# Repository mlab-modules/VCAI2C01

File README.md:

<!--- PrjInfo ---> <!--- Please remove this line after manually editing --->
<!--- 00a56be08b96043df9e37d6aff7b6990 --->
<!--- Created:2019-02-18 14:36:04.428293: ---> 
<!--- Author:: ---> 
<!--- AuthorEmail:: ---> 
<!--- Tags:: ---> 
<!--- Ust:: ---> 
<!--- Label --->
<!--- ELabel ---> 
<!--- Name:VCAI2C01A: --->
# VCAI2C01A
<!--- LongName --->
## AD converter voltage and current with I2C
<!--- ELongName ---> 

<!--- Lead --->
4-channel 18-bit AD converter voltage and current for industrial sensors. Ranges: 0-5V, 0-10V, 0-20mA, 4-20mA, 0-40 mA.
<!--- ELead ---> 

<!--- Description --->
<!--- EDescription --->
<!--- Content --->
<!--- EContent --->
<sub><sup> Generated with [MLABweb](https://github.com/MLAB-project/MLABweb). (2019-02-18)</sup></sub>

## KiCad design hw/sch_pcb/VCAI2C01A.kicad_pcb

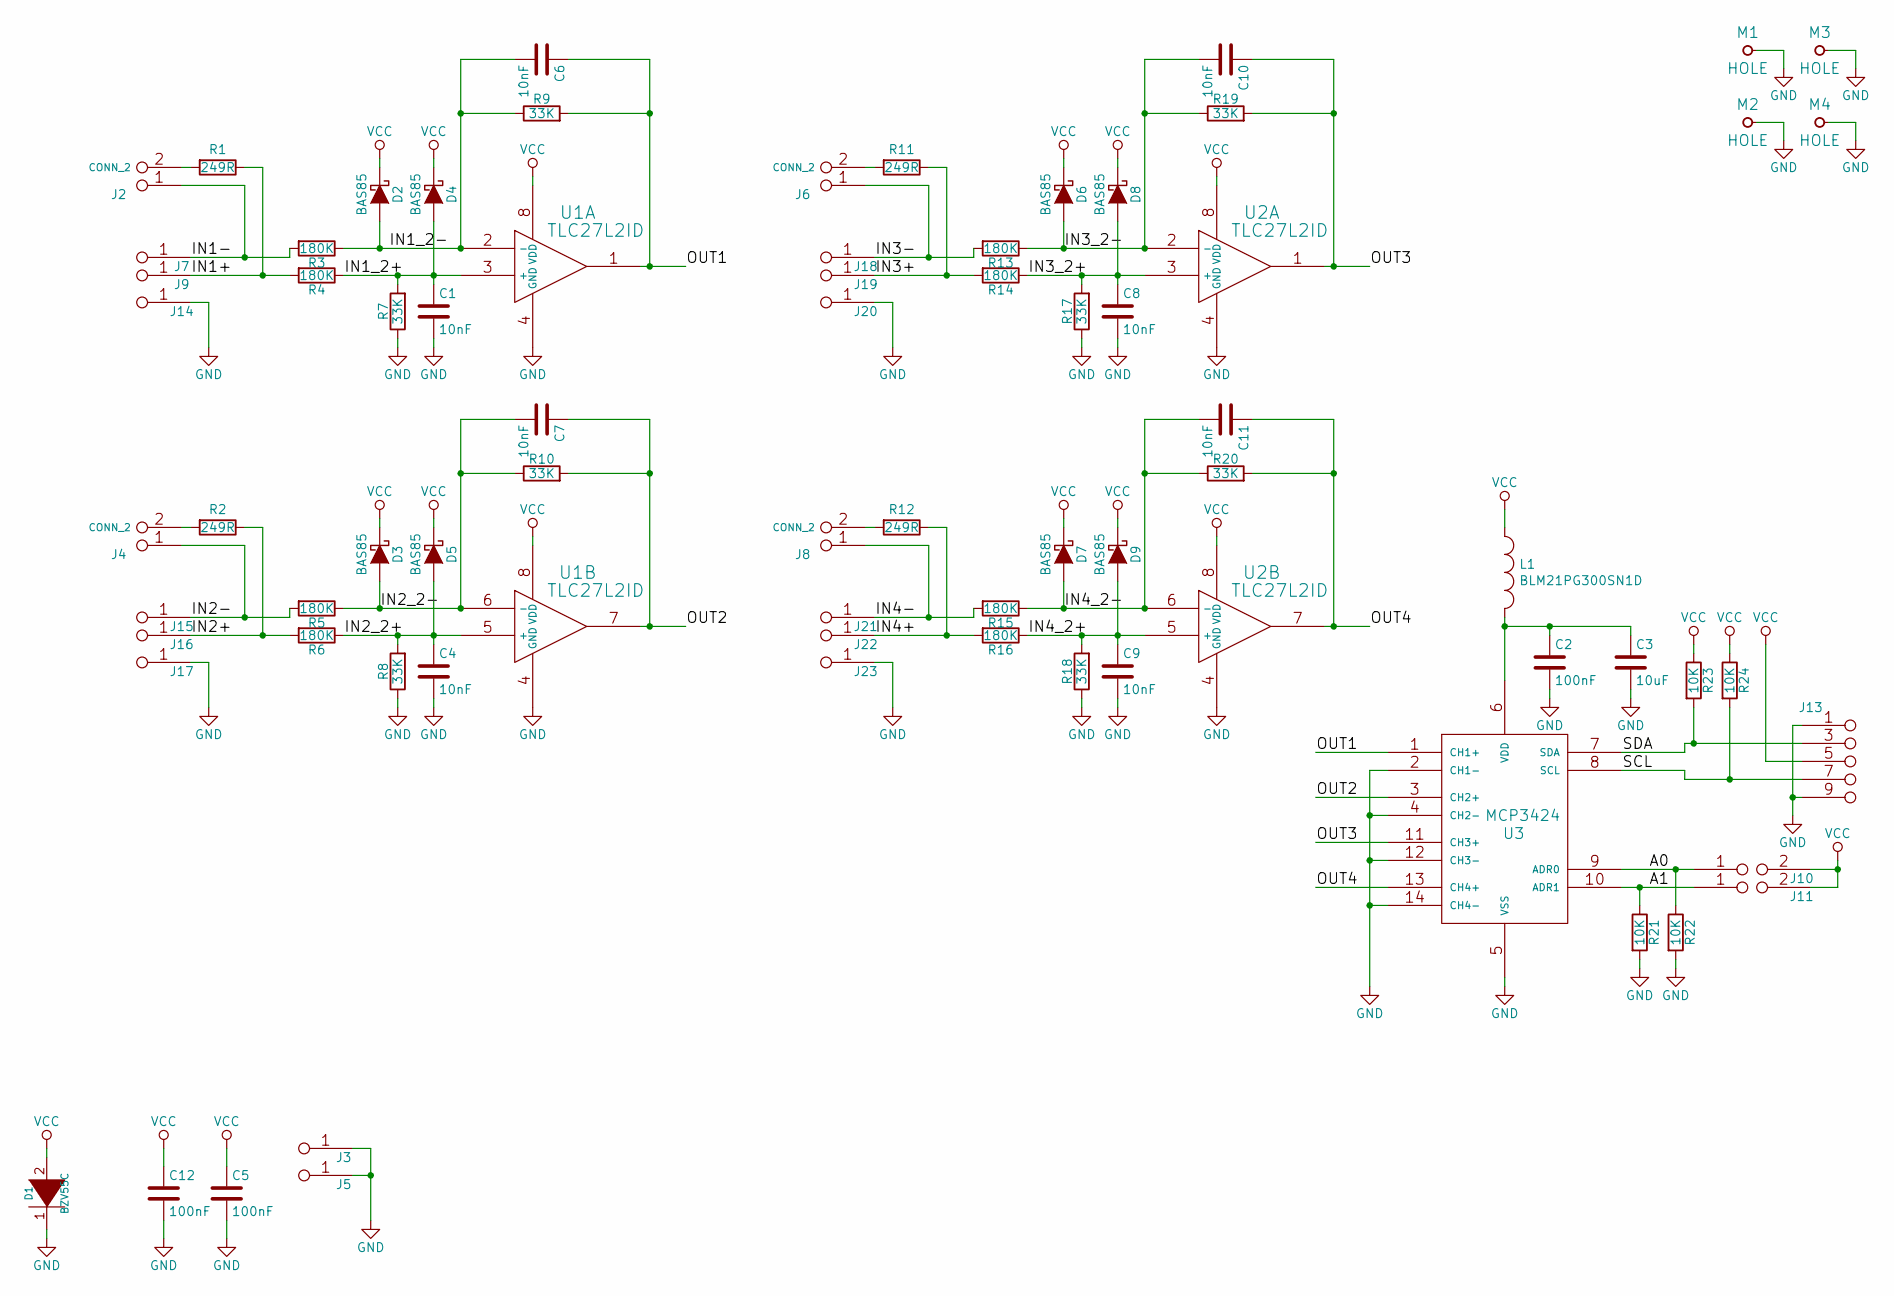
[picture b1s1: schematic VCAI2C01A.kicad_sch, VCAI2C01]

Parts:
C1, C4, C6, C7, C8, C9, C10, C11: 10nF; SMD-0805
C2, C5, C12: 100nF; SMD-0805
C3: 10uF; SMD-0805
D1: BZV55C; Diode-MiniMELF_Standard
D2, D3, D4, D5, D6, D7, D8, D9: BAS85; MiniMELF_Standard
J2, J4, J6, J8: CONN_2; Straight_1x02
J3: JUMP_2x1; Straight_2x01
J5, J7, J9, J14, J15, J16, J17, J18, J19, J20, J21, J22, J23: JUMP_2x1; Straight_1x02
J10, J11: JUMP2_2x1; Straight_2x01
J13: JUMP_5X2; Straight_2x05
L1: BLM21PG300SN1D; SMD-0805
M1, M2, M3, M4: HOLE; MountingHole_3mm
R1, R2, R11, R12: 249R; SMD-1206
R3, R4, R5, R6, R13, R14, R15, R16: 180K; SMD-0805
R7, R8, R9, R10, R17, R18, R19, R20: 33K; SMD-0805
R21, R22, R23, R24: 10K; SMD-0805
U1, U2: TLC27L2ID; SOIC-8_3.9x4.9mm_Pitch1.27mm
U3: MCP3424; SOIC-14

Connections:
/A0: J10.1, R22.1, U3.9 (ADR0)
/A1: J11.1, R21.1, U3.10 (ADR1)
/IN1+: J9.1, J9.2, R1.1, R4.2
/IN1-: J2.1, J7.1, J7.2, R3.2
/IN1_2+: C1.1, D4.2 (A), R4.1, R7.2, U1.3 (+)
/IN1_2-: C6.2, D2.2 (A), R3.1, R9.1, U1.2 (-)
/IN2+: J16.1, J16.2, R2.1, R6.2
/IN2-: J4.1, J15.1, J15.2, R5.2
/IN2_2+: C4.1, D5.2 (A), R6.1, R8.2, U1.5 (+)
/IN2_2-: C7.2, D3.2 (A), R5.1, R10.1, U1.6 (-)
/IN3+: J19.1, J19.2, R11.1, R14.2
/IN3-: J6.1, J18.1, J18.2, R13.2
/IN3_2+: C8.1, D8.2 (A), R14.1, R17.2, U2.3 (+)
/IN3_2-: C10.2, D6.2 (A), R13.1, R19.1, U2.2 (-)
/IN4+: J22.1, J22.2, R12.1, R16.2
/IN4-: J8.1, J21.1, J21.2, R15.2
/IN4_2+: C9.1, D9.2 (A), R16.1, R18.2, U2.5 (+)
/IN4_2-: C11.2, D7.2 (A), R15.1, R20.1, U2.6 (-)
/OUT1: C6.1, R9.2, U1.1, U3.1 (CH1+)
/OUT2: C7.1, R10.2, U1.7, U3.3 (CH2+)
/OUT3: C10.1, R19.2, U2.1, U3.11 (CH3+)
/OUT4: C11.1, R20.2, U2.7, U3.13 (CH4+)
/SCL: J13.7, J13.8 (7), R24.2, U3.8 (SCL)
/SDA: J13.3 (4), J13.4, R23.2, U3.7 (SDA)
GND: C1.2, C2.2, C3.2, C4.2, C5.2, C8.2, C9.2, C12.2, D1.1 (K), J3.1, J3.2, J5.1, J5.2, J13.1 (2), J13.2, J13.9 (10), J13.10, J14.1, J14.2, J17.1, J17.2, J20.1, J20.2, J23.1, J23.2, M1.1, M2.1, M3.1, M4.1, R7.1, R8.1, R17.1, R18.1, R21.2, R22.2, U1.4 (GND), U2.4 (GND), U3.2 (CH1-), U3.4 (CH2-), U3.5 (VSS), U3.12 (CH3-), U3.14 (CH4-)
unnamed: C2.1, C3.1, L1.2, U3.6 (VDD)
unnamed: J2.2 (PM), R1.2
unnamed: J4.2 (PM), R2.2
unnamed: J6.2 (PM), R11.2
unnamed: J8.2 (PM), R12.2
VCC: C5.1, C12.1, D1.2 (A), D2.1 (K), D3.1 (K), D4.1 (K), D5.1 (K), D6.1 (K), D7.1 (K), D8.1 (K), D9.1 (K), J10.2, J11.2, J13.5 (6), J13.6, L1.1, R23.1, R24.1, U1.8 (VDD), U2.8 (VDD)

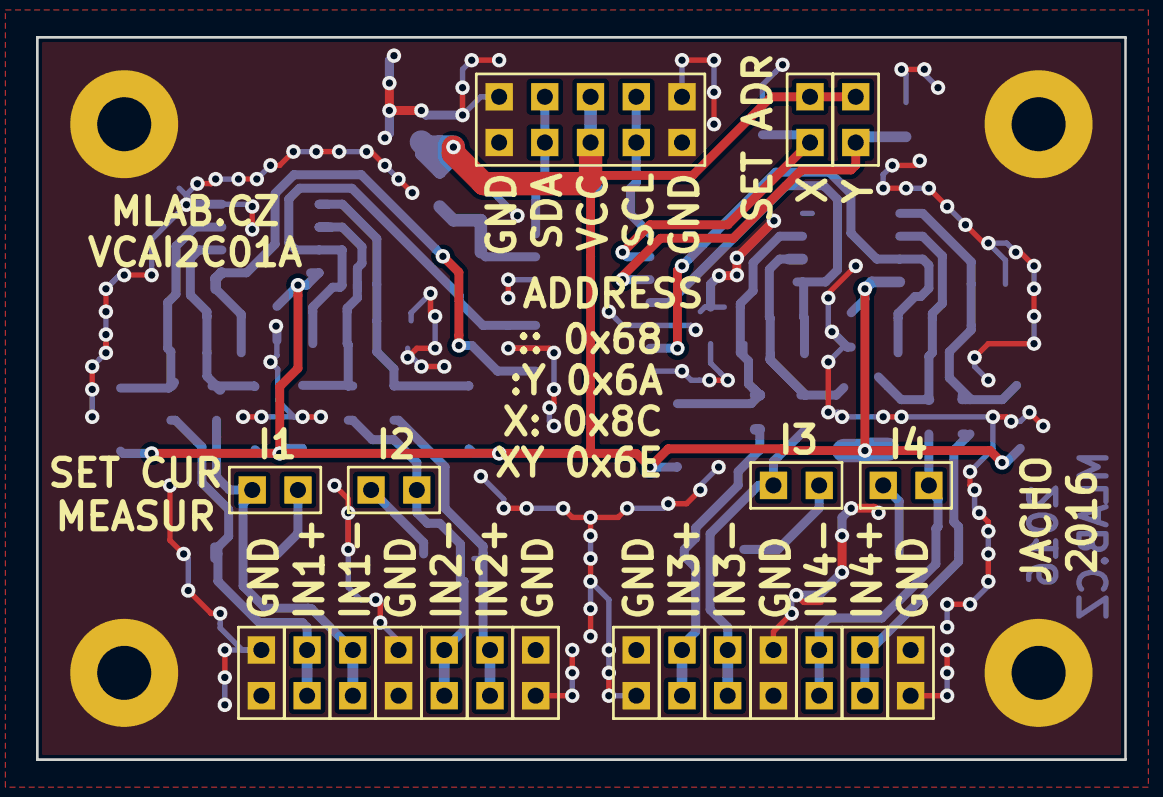
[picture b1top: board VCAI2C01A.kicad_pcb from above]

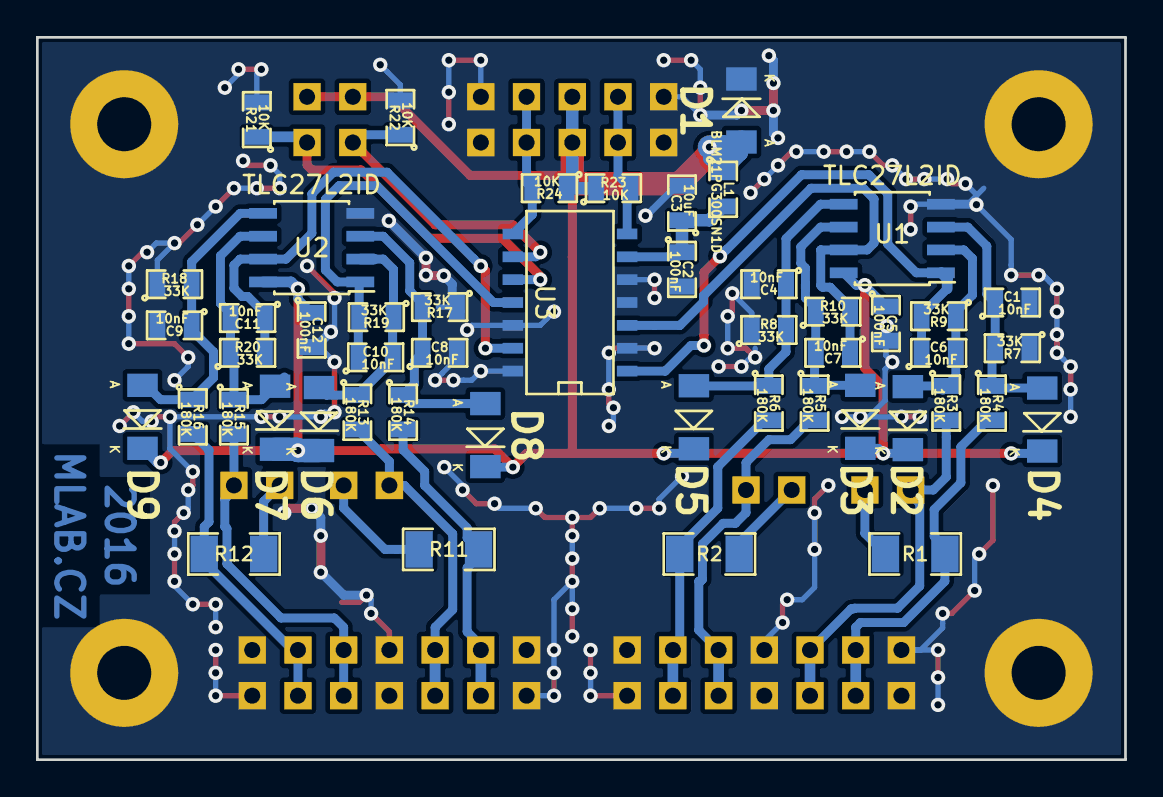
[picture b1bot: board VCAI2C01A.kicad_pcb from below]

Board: 2 copper layers, 60.5 x 40.1 mm, 74 parts (49 on the bottom side), 31 nets.

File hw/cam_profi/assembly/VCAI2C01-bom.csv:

Component,Description,Part,References,Value,Footprint,Quantity Per PCB,Datasheet
1,,C,C1C4C6C7C8C9C10C11,10nF,SMD-0805,8,
2,,C,C2C5C12,100nF,SMD-0805,3,
3,,C,C3,10uF,SMD-0805,1,
4,,D_Schottky,D2D3D4D5D6D7D8D9,BAS85,MiniMELF_Standard,8,
5,,DIODE,D1,BZV55C,Diode-MiniMELF_Standard,1,
6,,CONN_2,J2J4J6J8,CONN_2,Straight_1x02,4,
7,,JUMP2_2x1,J10J11,JUMP2_2x1,Straight_2x01,2,
8,,JUMP_2x1,J5J7J9J14J15J16J17J18J19J20J21J22J23,JUMP_2x1,Straight_1x02,13,
9,,JUMP_2x1,J3,JUMP_2x1,Straight_2x01,1,
10,,JUMP_5X2,J13,JUMP_5X2,Straight_2x05,1,
11,,INDUCTOR_SMALL,L1,BLM21PG300SN1D,SMD-0805,1,
12,,R,R1R2R11R12,249R,SMD-1206,4,
13,,R,R21R22R23R24,10K,SMD-0805,4,
14,,R,R7R8R9R10R17R18R19R20,33K,SMD-0805,8,
15,,R,R3R4R5R6R13R14R15R16,180K,SMD-0805,8,
16,,MCP3424,U3,MCP3424,SOIC-14,1,
17,,TLC27L2ID,U1U2,TLC27L2ID,SOIC-8_3.9x4.9mm_Pitch1.27mm,2,

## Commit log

2017-08-24 Microcontrollers and processors moved to separate directory.
2018-02-26 Oprava spatnych cest po prenosu dokumentu
2018-02-26 repair DB
2018-02-26 [MLABweb] 2018-02-26 00:42:19 ADCoctoSPI01A
2018-02-26 [MLABweb] 2018-02-26 00:42:31 SPIDIFF01A
2018-11-05 Presun obrazku do slozky img. Pregenerovani dokumentaci.
2019-02-18 [MLABweb] Documentaion edits; VCAI2C01A
2022-07-12 Update to kicad 6.0 Activate github workflow.
2022-07-12 commit of workflow directory.
2022-07-12 Update actions products
2022-10-12 Cleanup copper pour layout. Add powerflags to schematics.
2022-10-12 Move Front silkscreen back on board.
2023-03-02 Rename to the new MLAB convention.
2023-03-02 Update submodule and workflow.
2023-03-02 Update metadata files
2023-03-05 Update workflow files
2023-05-25 automated commit; add github actions
2023-07-05 automated commit; rename source files to new naming convence
2023-09-16 Update status
2023-09-17 Update metadata.yaml
    select title image.
